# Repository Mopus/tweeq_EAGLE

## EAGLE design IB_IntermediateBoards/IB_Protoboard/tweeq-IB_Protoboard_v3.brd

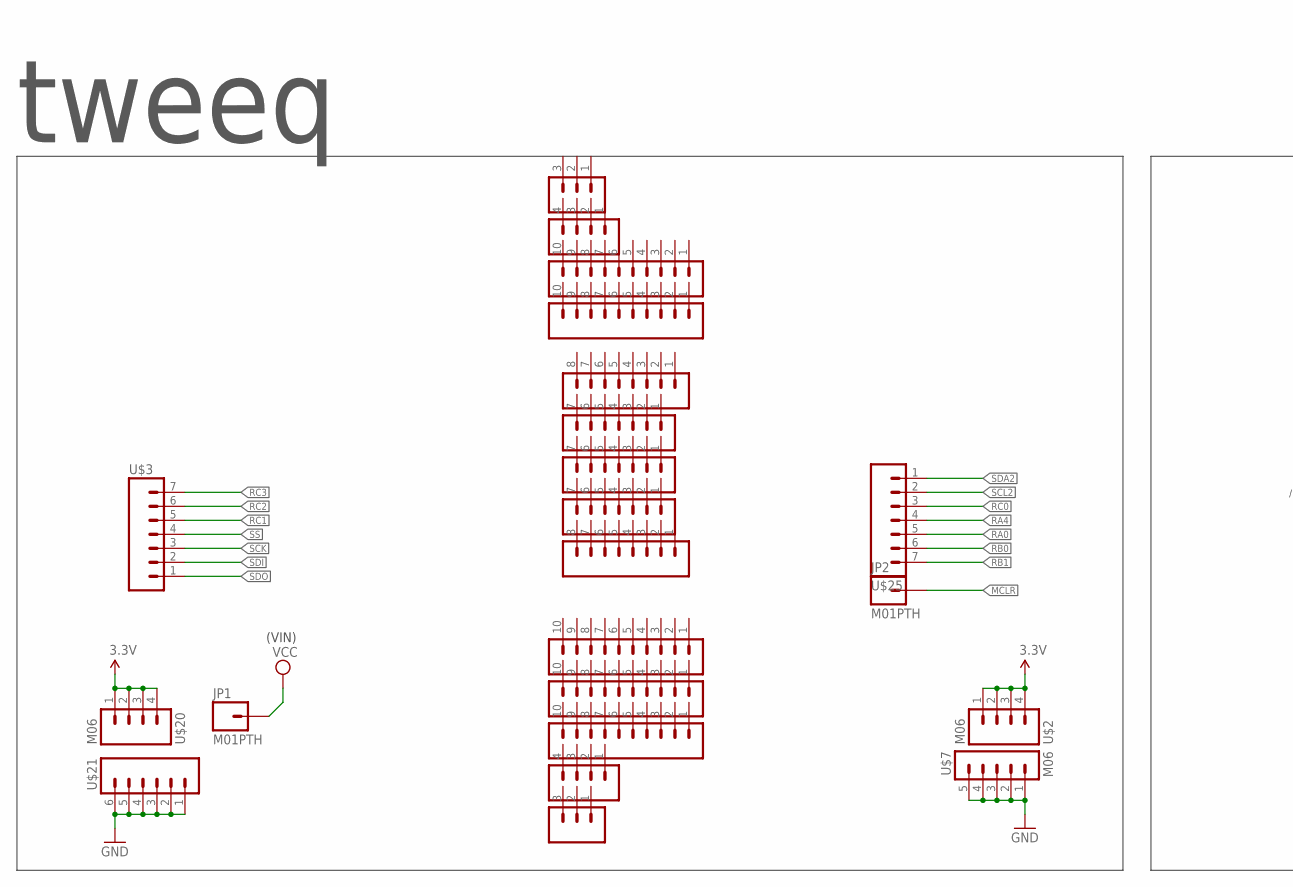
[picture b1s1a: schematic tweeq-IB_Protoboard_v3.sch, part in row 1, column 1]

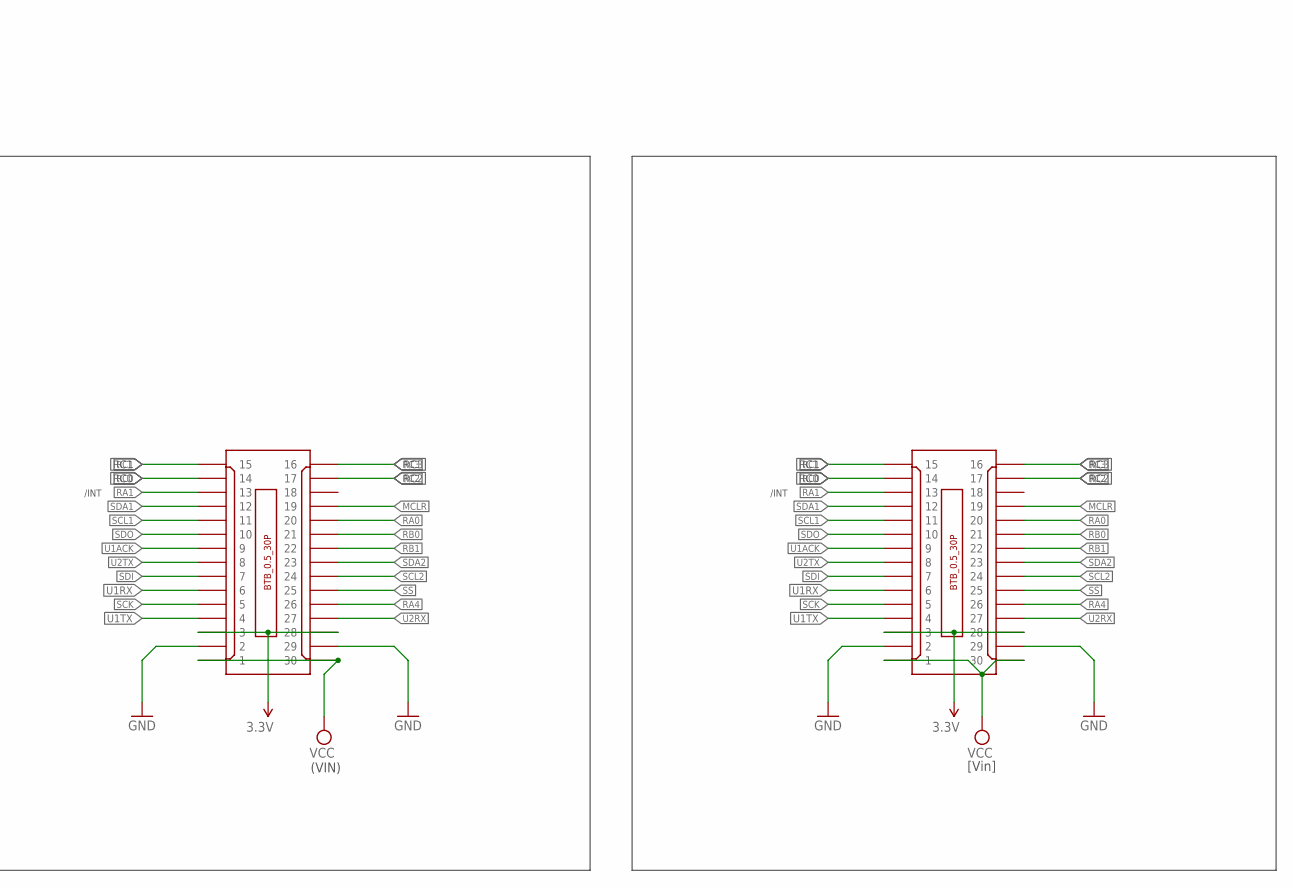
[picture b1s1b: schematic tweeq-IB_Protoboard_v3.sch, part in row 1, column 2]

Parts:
JP1, JP2: M01PTH; 1X01
U$2, U$20: M06; 1X04_NS_ROUND
U$3, U$25: M072.54NOSILK; 1X07_NOSILK_
U$4: BTB_CONN_30P/F; BTB0.5-30F-3.0G
U$5, U$19: M10-1/NS-SQ; 1X03-NS-SQ
U$7: M06; 1X05-NS-SQ
U$8: M09; 1X10-NS-SQ
U$9: M09; 1X08-NS-SQ
U$10, U$11, U$12: M09; 1X07-NS-SQ
U$13: M10-10.1; 1X08-NS-SQ
U$14, U$15, U$16, U$18: M10-1/NS-SQ; 1X10-NS-SQ
U$17, U$23: M10-1/NS-SQ; 1X04-NS-SQ
U$21: M06NS-SQ; 1X06-NS-SQ
U$22: BTB_CONN_30P/M; BTB0.5-30M-3.0G

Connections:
3.3V: U$2.1, U$2.2, U$2.3, U$2.4, U$4.3, U$4.28, U$20.1, U$20.2, U$20.3, U$20.4, U$22.3, U$22.28
GND: U$4.2, U$4.29, U$7.1, U$7.2, U$7.3, U$7.4, U$7.5, U$21.1, U$21.2, U$21.3, U$21.4, U$21.5, U$21.6, U$22.2, U$22.29
MCLR: JP2.1, U$4.19, U$22.19
RA0: U$4.20, U$22.20, U$25.5
RA1: U$4.13, U$22.13
RA4: U$4.26, U$22.26, U$25.4
RB0: U$4.21, U$22.21, U$25.6
RB1: U$4.22, U$22.22, U$25.7
RC0: U$4.14, U$22.14, U$25.3
RC1: U$3.5, U$4.15, U$22.15
RC2: U$3.6, U$4.17, U$22.17
RC3: U$3.7, U$4.16, U$22.16
SCK: U$3.3, U$4.5, U$22.5
SCL1: U$4.11, U$22.11
SCL2: U$4.24, U$22.24, U$25.2
SDA1: U$4.12, U$22.12
SDA2: U$4.23, U$22.23, U$25.1
SDI: U$3.2, U$4.7, U$22.7
SDO: U$3.1, U$4.10, U$22.10
SS: U$3.4, U$4.25, U$22.25
U1ACK: U$4.9, U$22.9
U1RX: U$4.6, U$22.6
U1TX: U$4.4, U$22.4
U2RX: U$4.27, U$22.27
U2TX: U$4.8, U$22.8
VCC: JP1.1, U$4.1, U$4.30, U$22.1, U$22.30

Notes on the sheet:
tweeq
(VIN)
/INT
[Vin]

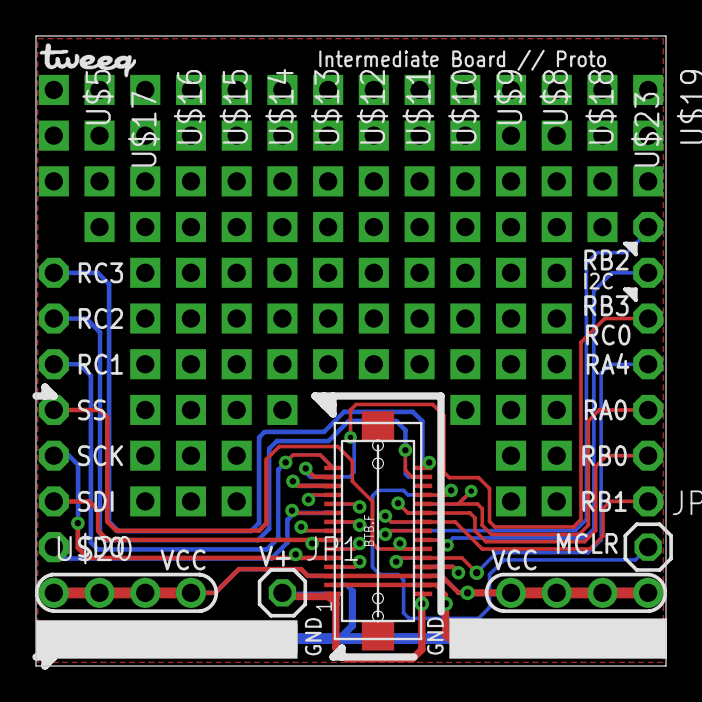
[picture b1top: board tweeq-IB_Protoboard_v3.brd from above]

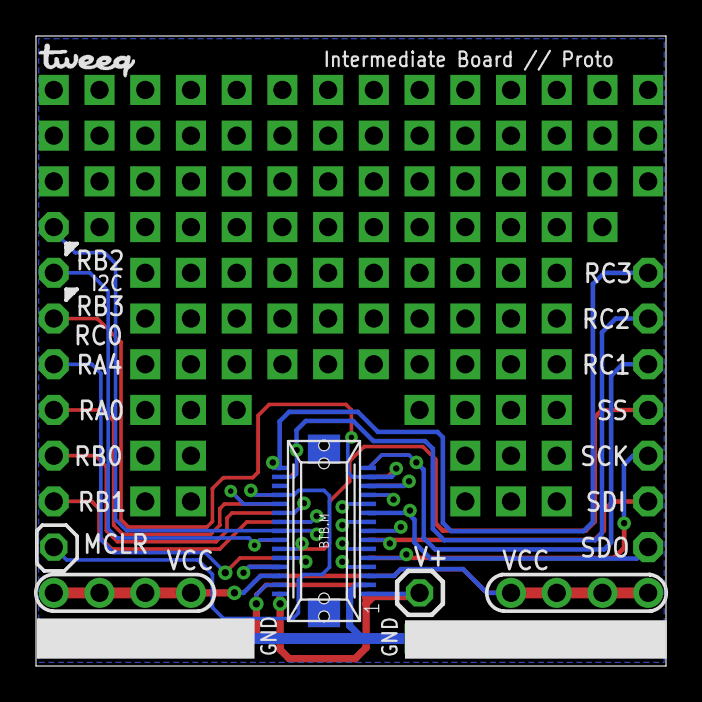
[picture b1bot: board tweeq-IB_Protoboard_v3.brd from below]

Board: 2 copper layers, 35.0 x 35.0 mm, 26 parts (2 on the bottom side), 26 nets.

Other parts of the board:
U$1, U$24: TWEEQ-LOGO-S

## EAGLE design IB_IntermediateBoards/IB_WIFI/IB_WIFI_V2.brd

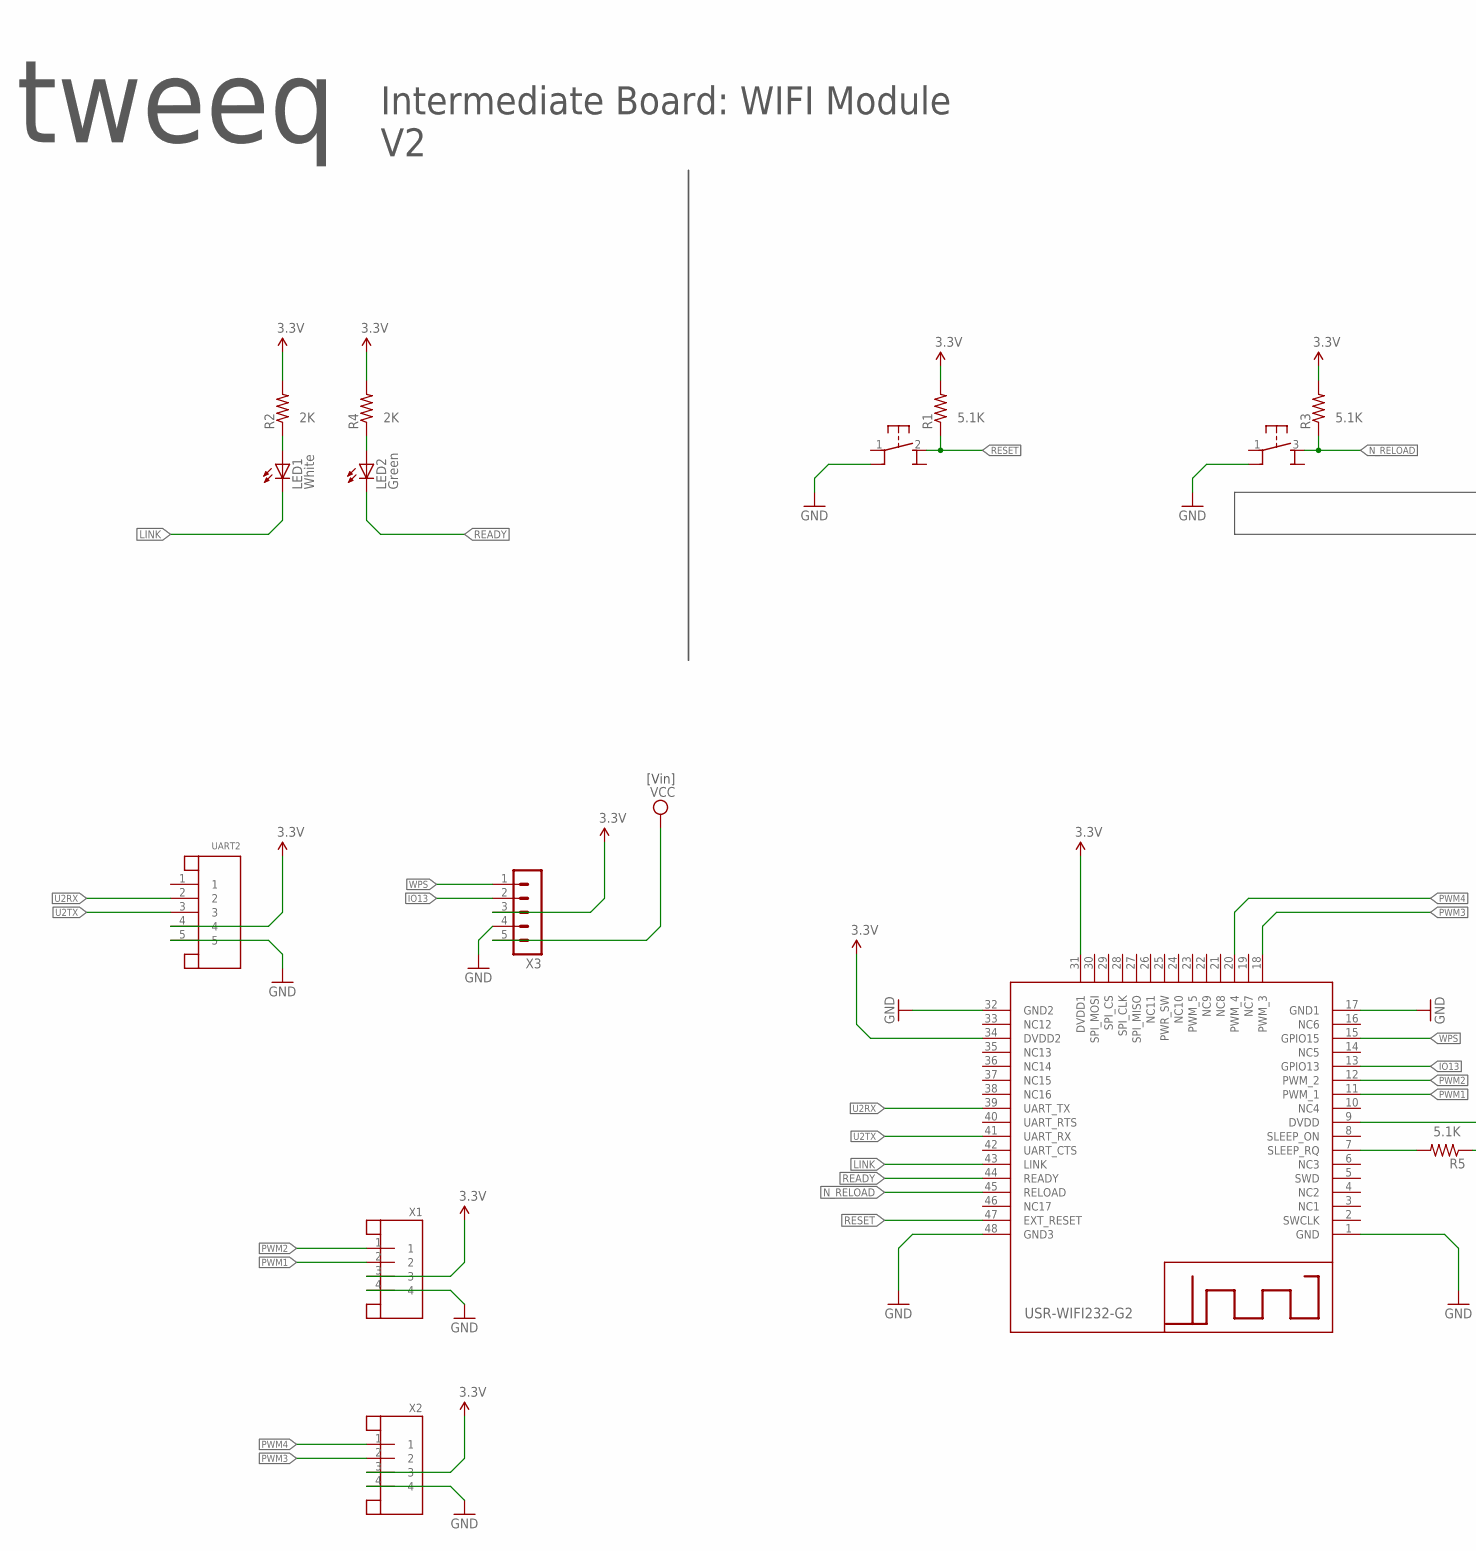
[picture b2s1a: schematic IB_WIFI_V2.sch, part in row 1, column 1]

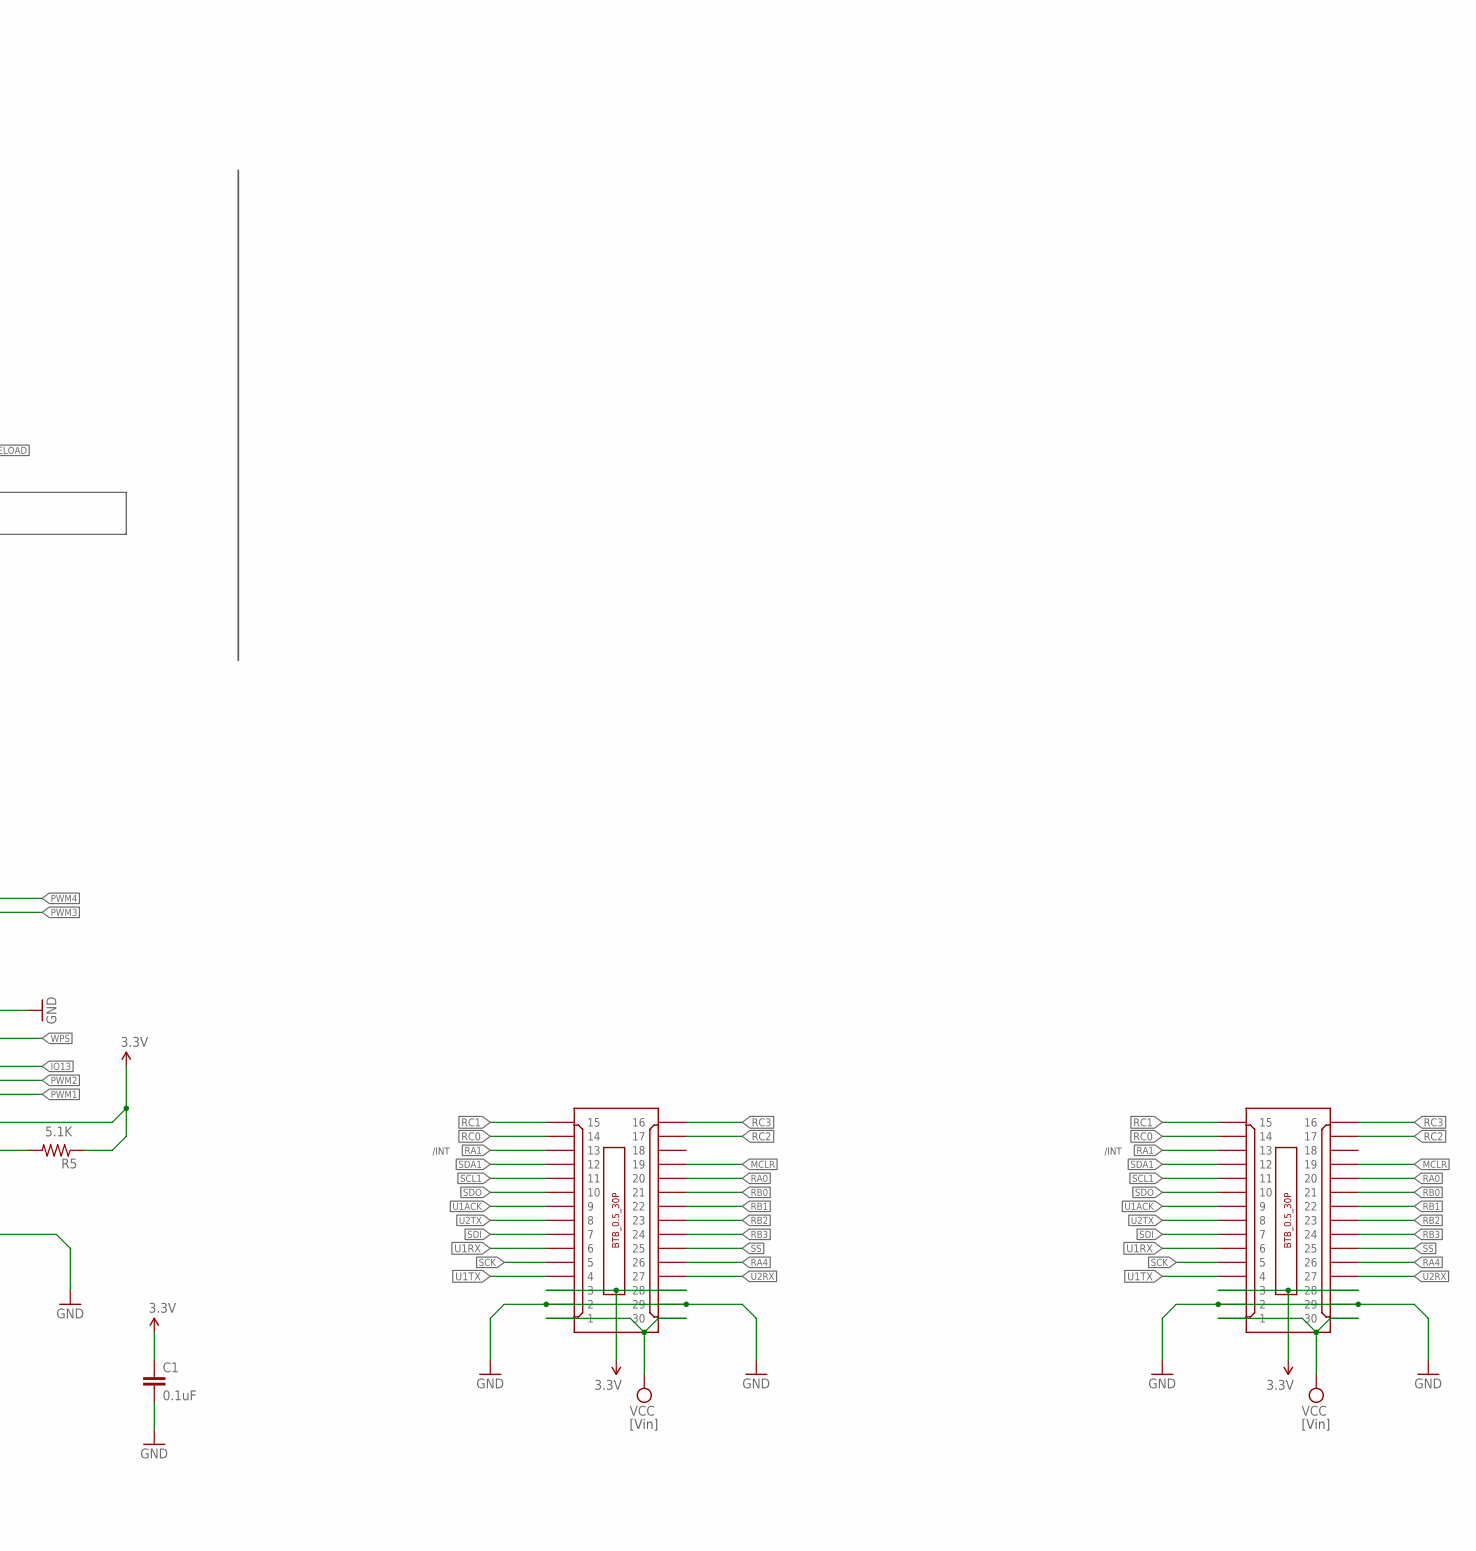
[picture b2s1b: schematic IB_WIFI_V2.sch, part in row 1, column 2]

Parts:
C1: 0.1uF; C0603
LED1: White; CHIPLED_0805
LED2: Green; CHIPLED_0805
R1, R3, R5: 5.1K; R0603
R2, R4: 2K; R0603
U$1: BTB_CONN_30P/M; BTB0.5-30M-3.0G
U$3: BTB_CONN_30P/F; BTB0.5-30F-3.0G
U$4: PB_MICRO_SMT; PB_SMT_3.5X3X2
U$5: PB_MICRO_SMTRIGHTANGLE; PB_SMT_90D6.2X4.6
UART2: JST-5PINSH; SH1.0-5PIN
USR-WIFI232-G2: USR-WIFI232-G2; USR-WIFI232-G
X1, X2: JST-4PINSH; SH1.0-4PIN
X3: M05-1PAD; 1X05_PAD

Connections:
3.3V: C1.1, R1.2, R2.2, R3.2, R4.2, R5.1, U$1.3, U$1.28, U$3.3, U$3.28, UART2.4, USR-WIFI232-G2.9 (DVDD), USR-WIFI232-G2.31 (DVDD1), USR-WIFI232-G2.34 (DVDD2), X1.3, X2.3, X3.3
GND: C1.2, U$1.2, U$1.29, U$3.2, U$3.29, U$4.2 (1A), U$5.1A, UART2.5, USR-WIFI232-G2.1 (GND), USR-WIFI232-G2.17 (GND1), USR-WIFI232-G2.32 (GND2), USR-WIFI232-G2.48 (GND3), X1.4, X2.4, X3.4
IO13: USR-WIFI232-G2.13 (GPIO13), X3.2
LINK: LED1.C, USR-WIFI232-G2.43 (LINK)
MCLR: U$1.19, U$3.19
unnamed: LED1.A, R2.1
unnamed: LED2.A, R4.1
N_RELOAD: R3.1, U$4.3 (2), USR-WIFI232-G2.45 (RELOAD)
PWM1: USR-WIFI232-G2.11 (PWM_1), X1.2
PWM2: USR-WIFI232-G2.12 (PWM_2), X1.1
PWM3: USR-WIFI232-G2.18 (PWM_3), X2.2
PWM4: USR-WIFI232-G2.20 (PWM_4), X2.1
RA0: U$1.20, U$3.20
RA1: U$1.13, U$3.13
RA4: U$1.26, U$3.26
RB0: U$1.21, U$3.21
RB1: U$1.22, U$3.22
RB2: U$1.23, U$3.23
RB3: U$1.24, U$3.24
RC0: U$1.14, U$3.14
RC1: U$1.15, U$3.15
RC2: U$1.17, U$3.17
RC3: U$1.16, U$3.16
READY: LED2.C, USR-WIFI232-G2.44 (READY)
RESET: R1.1, U$5.2, USR-WIFI232-G2.47 (EXT_RESET)
SCK: U$1.5, U$3.5
SCL1: U$1.11, U$3.11
SDA1: U$1.12, U$3.12
SDI: U$1.7, U$3.7
SDO: U$1.10, U$3.10
SLEEP_RQ: R5.2, USR-WIFI232-G2.7 (SLEEP_RQ)
SS: U$1.25, U$3.25
U1ACK: U$1.9, U$3.9
U1RX: U$1.6, U$3.6
U1TX: U$1.4, U$3.4
U2RX: U$1.27, U$3.27, UART2.2, USR-WIFI232-G2.39 (UART_TX)
U2TX: U$1.8, U$3.8, UART2.3, USR-WIFI232-G2.41 (UART_RX)
VCC: U$1.1, U$1.30, U$3.1, U$3.30, X3.5
WPS: USR-WIFI232-G2.15 (GPIO15), X3.1

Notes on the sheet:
tweeq
Intermediate Board: WIFI Module
[Vin]
/INT

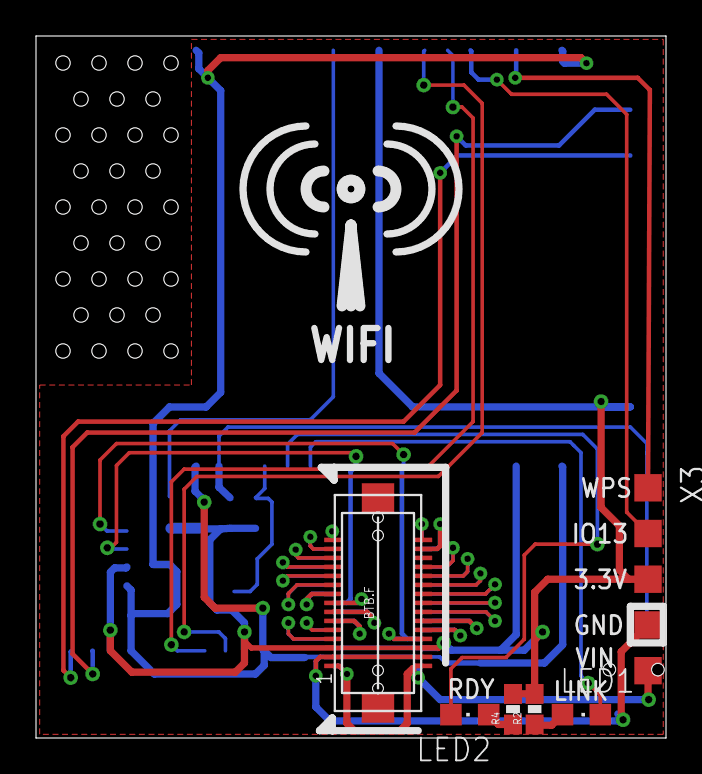
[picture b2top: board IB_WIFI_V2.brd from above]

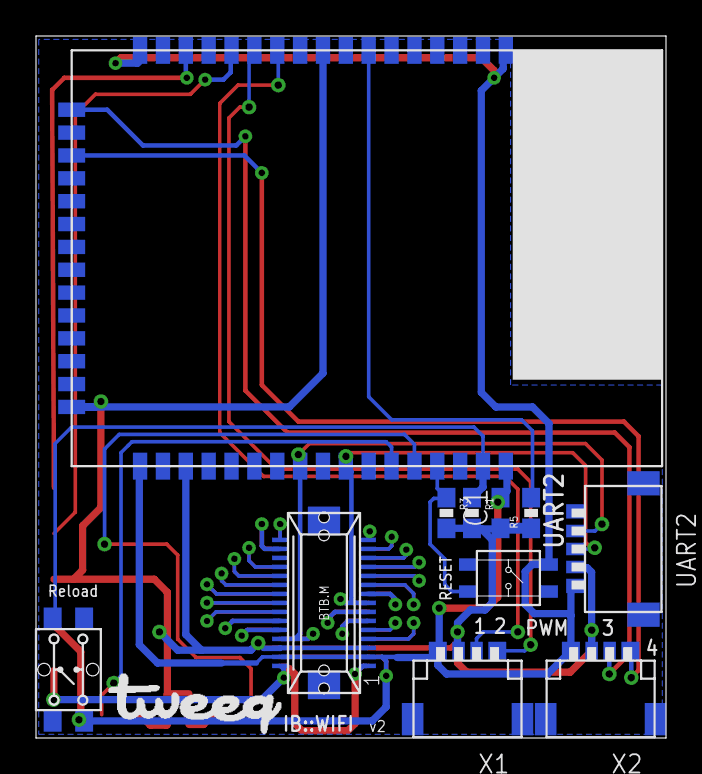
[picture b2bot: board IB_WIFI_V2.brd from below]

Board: 2 copper layers, 35.0 x 39.0 mm, 18 parts (12 on the bottom side), 39 nets.

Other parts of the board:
U$6: TWEEQ-LOGO-M

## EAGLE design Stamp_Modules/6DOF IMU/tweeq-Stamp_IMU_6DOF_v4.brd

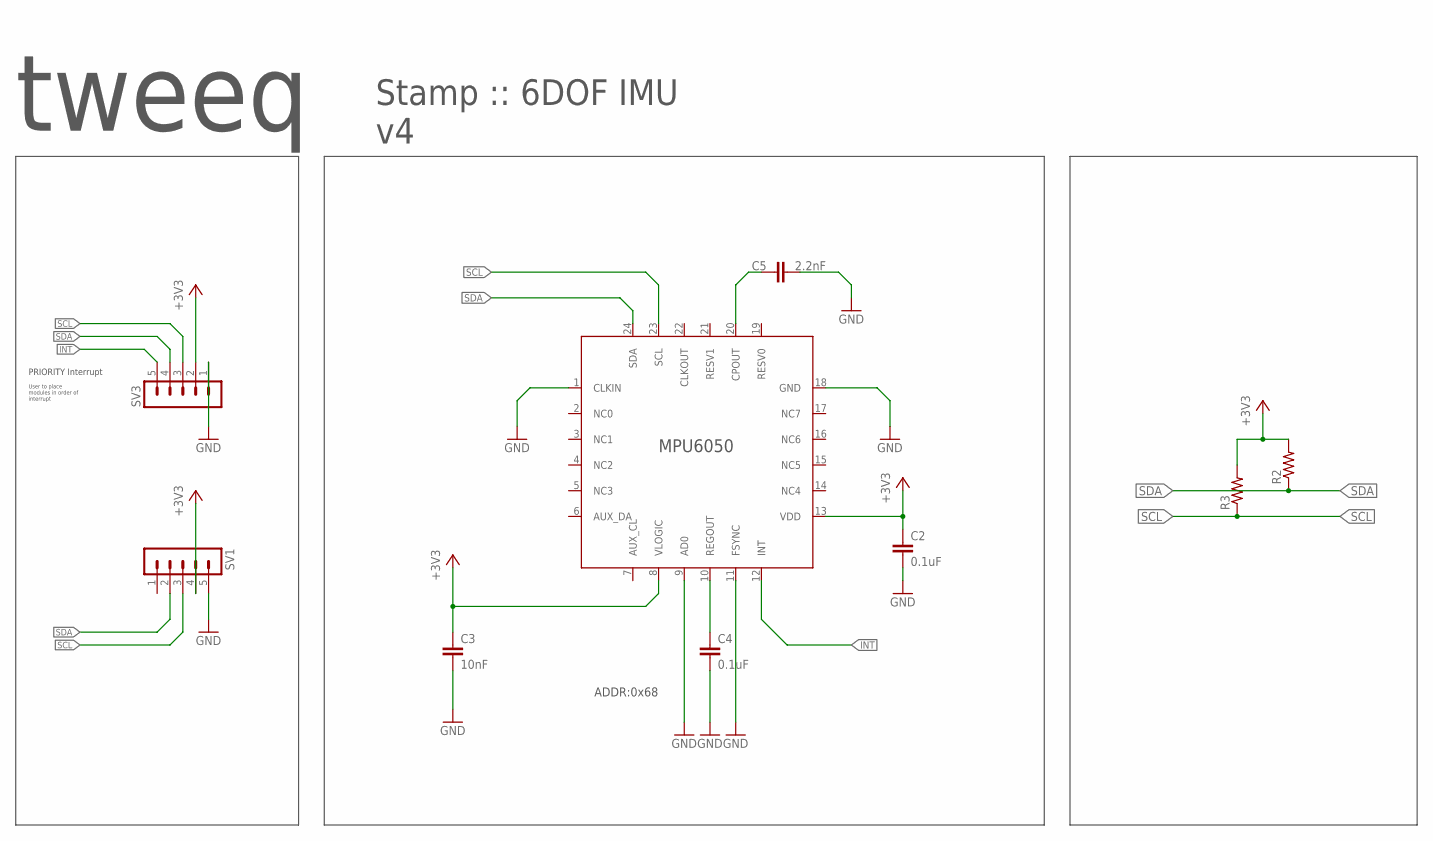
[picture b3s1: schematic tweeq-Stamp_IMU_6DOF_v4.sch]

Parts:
C2, C4: 0.1uF; C0603K
C3: 10nF; C0603K
C5: 2.2nF; C0603K
R2, R3: R-US_R0603; R0603
SV1, SV3: M05-1STAMP; 1X05-1.5MM-STAMP
U1: MPU6050; QFN24

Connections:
+3V3: C2.1, C3.1, R2.2, R3.2, SV1.4, SV3.2, U1.8 (VLOGIC), U1.13 (VDD)
GND: C2.2, C3.2, C4.2, C5.2, SV1.5, SV3.1, U1.1 (CLKIN), U1.9 (AD0), U1.11 (FSYNC), U1.18 (GND)
INT: SV3.5, U1.12 (INT)
unnamed: C5.1, U1.20 (CPOUT)
unnamed: C4.1, U1.10 (REGOUT)
SCL: R3.1, SV1.3, SV3.3, U1.23 (SCL)
SDA: R2.1, SV1.2, SV3.4, U1.24 (SDA)

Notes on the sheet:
PRIORITY Interrupt
User to place modules in order of interrupt
MPU6050
ADDR:0x68
tweeq
Stamp :: 6DOF IMU v4

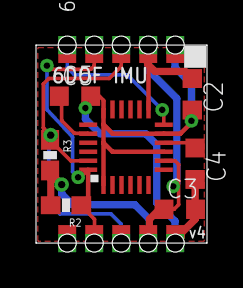
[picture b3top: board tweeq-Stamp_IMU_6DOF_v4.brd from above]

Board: 2 copper layers, 9.5 x 11.0 mm, 10 parts (1 on the bottom side), 7 nets.

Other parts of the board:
U$1: TWEEQ-LOGO-S

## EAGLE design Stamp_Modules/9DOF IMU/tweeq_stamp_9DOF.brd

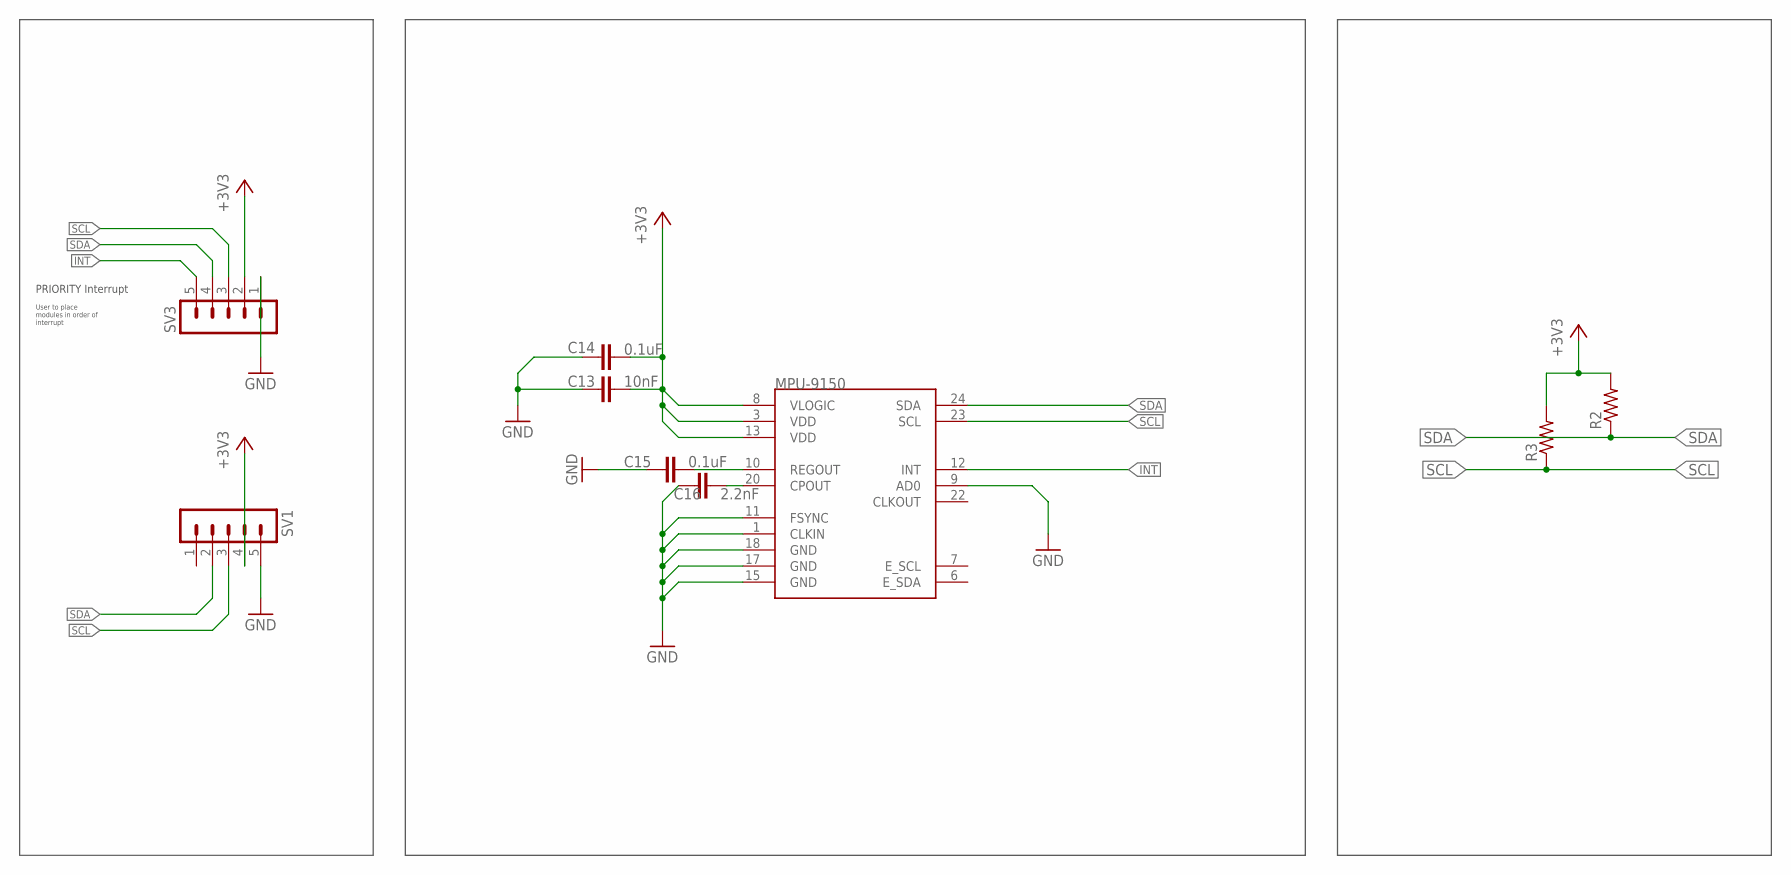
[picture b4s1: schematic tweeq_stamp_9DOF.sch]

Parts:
C13: 10nF; C0402K
C14, C15: 0.1uF; C0402K
C16: 2.2nF; C0402K
MPU-9150: MPU-9150QFN-24-NP; QFN-24-NP
R2, R3: R-US_R0402; R0402
SV1, SV3: M05-1STAMP; 1X05-1.5MM-STAMP

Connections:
+3V3: C13.2, C14.2, MPU-9150.3 (VDD), MPU-9150.8 (VLOGIC), MPU-9150.13 (VDD), R2.2, R3.2, SV1.4, SV3.2
GND: C13.1, C14.1, C15.1, C16.1, MPU-9150.1 (CLKIN), MPU-9150.9 (AD0), MPU-9150.11 (FSYNC), MPU-9150.15 (GND), MPU-9150.17 (GND), MPU-9150.18 (GND), SV1.5, SV3.1
INT: MPU-9150.12 (INT), SV3.5
unnamed: C16.2, MPU-9150.20 (CPOUT)
unnamed: C15.2, MPU-9150.10 (REGOUT)
SCL: MPU-9150.23 (SCL), R3.1, SV1.3, SV3.3
SDA: MPU-9150.24 (SDA), R2.1, SV1.2, SV3.4

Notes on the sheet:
PRIORITY Interrupt
User to place modules in order of interrupt

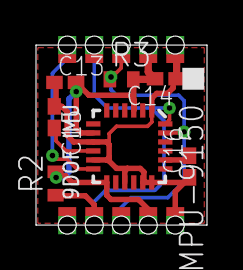
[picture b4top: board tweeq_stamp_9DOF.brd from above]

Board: 2 copper layers, 9.5 x 10.0 mm, 10 parts (1 on the bottom side), 7 nets.

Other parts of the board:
U$1: TWEEQ-LOGO-S

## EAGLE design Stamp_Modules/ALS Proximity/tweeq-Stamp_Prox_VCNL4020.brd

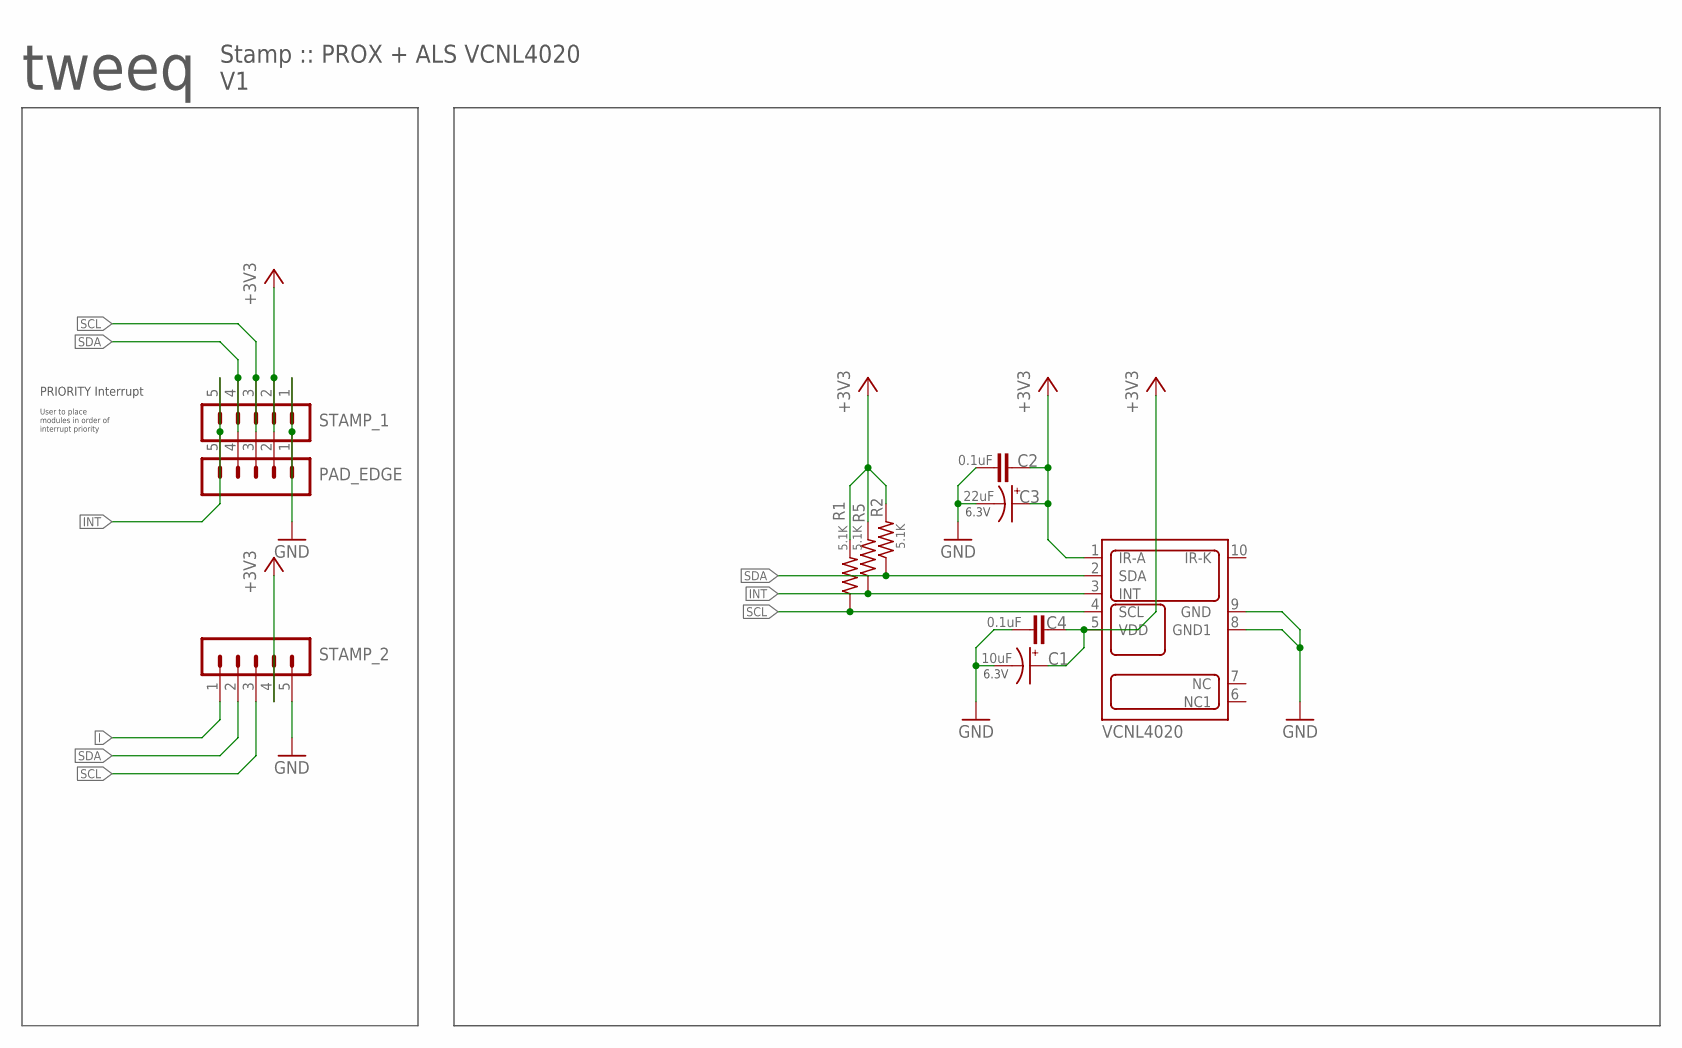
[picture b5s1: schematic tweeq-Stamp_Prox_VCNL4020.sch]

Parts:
C1: 10uF; SMC_Z
C2, C4: 0.1uF; C0402K
C3: 22uF; SMC_Z
PAD_EDGE: M05-11.5MM-PAD; 1X05-1.5MM-PAD
R1, R2, R5: 5.1K; R0402
STAMP_1, STAMP_2: M05-1STAMP; 1X05-1.5MM-STAMP
VCNL4020: VCNL4020

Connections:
+3V3: C1.+, C2.2, C3.+, C4.2, PAD_EDGE.2, R1.2, R2.2, R5.2, STAMP_1.2, STAMP_2.4, VCNL4020.1 (IR-A), VCNL4020.5 (VDD)
GND: C1.-, C2.1, C3.-, C4.1, PAD_EDGE.1, STAMP_1.1, STAMP_2.5, VCNL4020.8 (GND1), VCNL4020.9 (GND)
I: STAMP_2.1
INT: PAD_EDGE.5, R5.1, STAMP_1.5, VCNL4020.3 (INT)
SCL: PAD_EDGE.3, R1.1, STAMP_1.3, STAMP_2.3, VCNL4020.4 (SCL)
SDA: PAD_EDGE.4, R2.1, STAMP_1.4, STAMP_2.2, VCNL4020.2 (SDA)

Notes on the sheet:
tweeq
Stamp :: PROX + ALS VCNL4020 V1
PRIORITY Interrupt
User to place modules in order of interrupt priority
6.3V

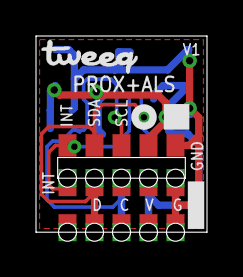
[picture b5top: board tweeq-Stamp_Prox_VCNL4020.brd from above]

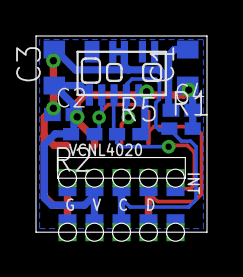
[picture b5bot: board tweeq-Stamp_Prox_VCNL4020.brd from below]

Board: 2 copper layers, 9.5 x 10.9 mm, 12 parts (8 on the bottom side), 5 nets.

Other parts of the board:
U$1: TWEEQ-LOGO-S

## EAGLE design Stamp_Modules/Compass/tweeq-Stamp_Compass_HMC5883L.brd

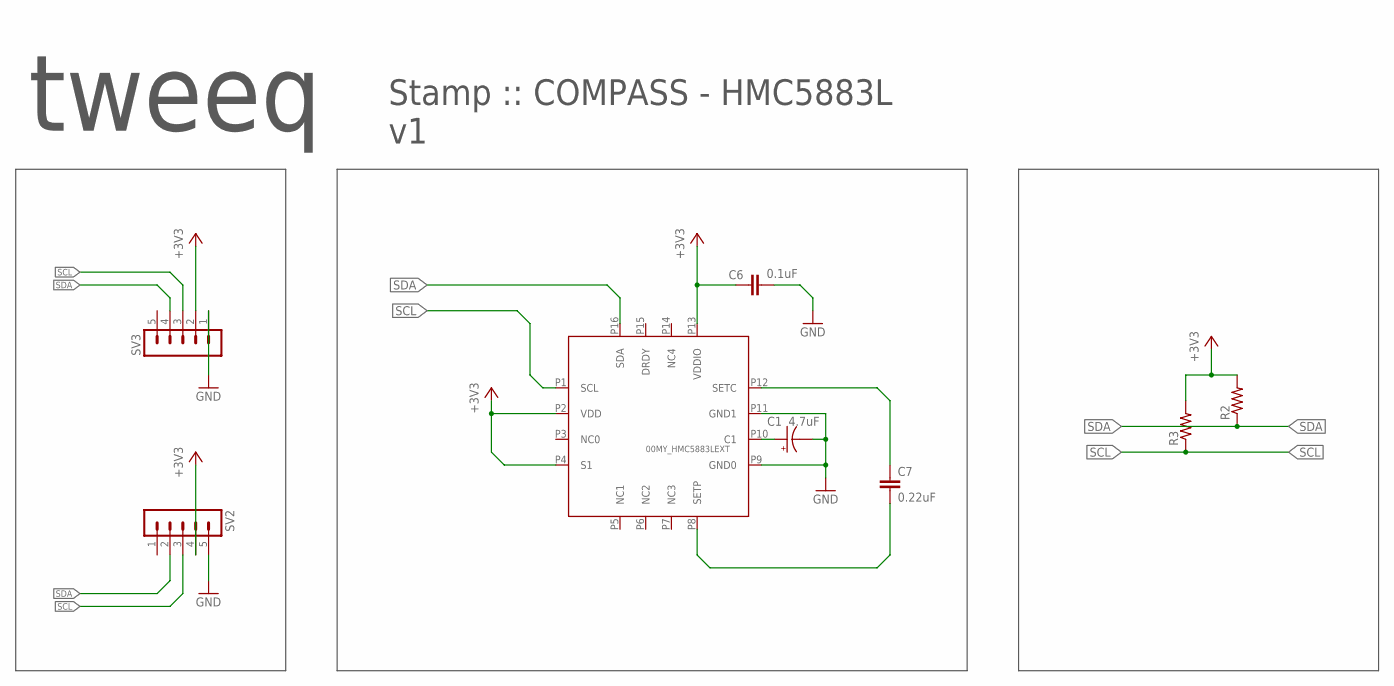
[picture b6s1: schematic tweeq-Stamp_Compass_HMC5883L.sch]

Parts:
C1: 4.7uF; SMC_A
C6: 0.1uF; C0603K
C7: 0.22uF; C0603K
R2, R3: R-US_R0402; R0402
SV2, SV3: M05-1STAMP; 1X05-1.5MM-STAMP
U$4: 00MY_HMC5883LEXT; LPCC16_EXT

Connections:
+3V3: C6.1, R2.2, R3.2, SV2.4, SV3.2, U$4.P2 (VDD), U$4.P4 (S1), U$4.P13 (VDDIO)
GND: C1.-, C6.2, SV2.5, SV3.1, U$4.P9 (GND0), U$4.P11 (GND1)
unnamed: C1.+, U$4.P10 (C1)
unnamed: C7.1, U$4.P12 (SETC)
unnamed: C7.2, U$4.P8 (SETP)
SCL: R3.1, SV2.3, SV3.3, U$4.P1 (SCL)
SDA: R2.1, SV2.2, SV3.4, U$4.P16 (SDA)

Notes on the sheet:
tweeq
Stamp :: COMPASS - HMC5883L v1

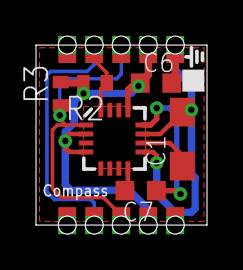
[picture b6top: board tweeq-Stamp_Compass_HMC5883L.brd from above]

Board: 2 copper layers, 9.5 x 10.0 mm, 9 parts (1 on the bottom side), 7 nets.

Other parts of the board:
U$1: TWEEQ-LOGO-S

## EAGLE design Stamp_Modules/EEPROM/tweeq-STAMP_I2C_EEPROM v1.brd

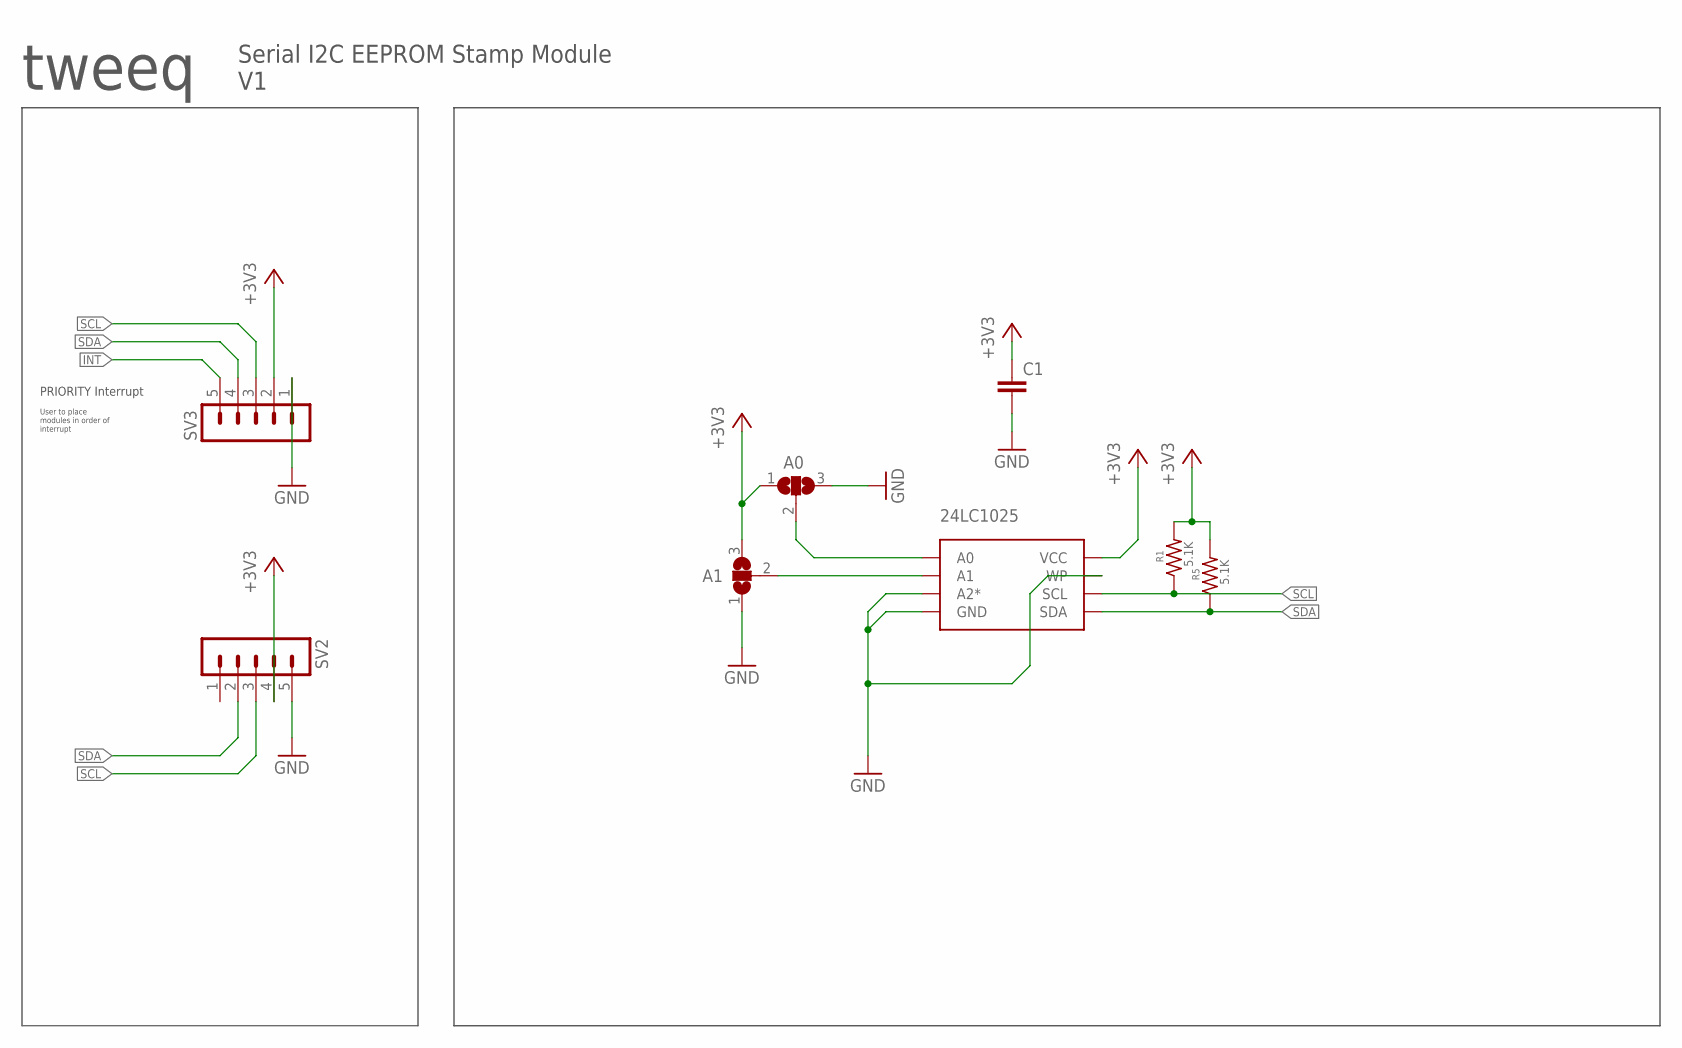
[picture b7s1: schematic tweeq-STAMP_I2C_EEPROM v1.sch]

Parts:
24LC1025: 24LC1025; SOIC8(W)
A0, A1: JUMPER_SJ2WS; JUMPER_SJ_S
C1: C-EUC0402K; C0402K
R1, R5: 5.1K; R0402
SV2, SV3: M05-1STAMP; 1X05-1.5MM-STAMP

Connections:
+3V3: 24LC1025.8 (VCC), A0.1, A1.3, C1.1, R1.2, R5.2, SV2.4, SV3.2
GND: 24LC1025.3 (A2*), 24LC1025.4 (GND), 24LC1025.7 (WP), A0.3, A1.1, C1.2, SV2.5, SV3.1
INT: SV3.5
unnamed: 24LC1025.1 (A0), A0.2
unnamed: 24LC1025.2 (A1), A1.2
SCL: 24LC1025.6 (SCL), R1.1, SV2.3, SV3.3
SDA: 24LC1025.5 (SDA), R5.1, SV2.2, SV3.4

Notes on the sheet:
tweeq
Serial I2C EEPROM Stamp Module V1
PRIORITY Interrupt
User to place modules in order of interrupt

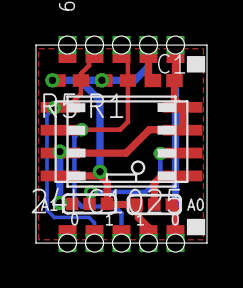
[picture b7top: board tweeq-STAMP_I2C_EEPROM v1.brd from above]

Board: 2 copper layers, 9.5 x 11.0 mm, 9 parts (1 on the bottom side), 6 nets.

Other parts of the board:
U$1: TWEEQ-LOGO-S

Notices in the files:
parts and their libraries:
SparkFun-Sensors: Licensing: Creative Commons ShareAlike 4.0 International - https://creativecommons.org/licenses/by-sa/4.0
